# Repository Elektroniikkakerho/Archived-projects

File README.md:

# Elektroniikkakerhon vanhoja projekteja

Tänne on arkistoitu vanhoja projekteja Sähköinsinöörikillan elektroniikkakerhon verkkosivuilta, jotka sijaitsivat vuoteen 2021 asti osoitteessa `http://www.ee.oulu.fi/~elekerho/`. Vaikka tekniikka onkin jo jättänyt osan näistä projekteista jälkeensä, toiset sopivat projekti-ideoiksi vielä tänäkin päivänä. Nämä tomuiset kertomukset voivat myös toimia inspiraationa omille ideoillesi.

### [AVR Speden Spelit](spelit/README.md)

### [Digitaalinen ajastin](ajastin/README.md)

### [Ledinäyttö](ledinaytto/README.md)

### [Ritariässä](ritariassa/README.md)

### [SCART-jäynä](scart/README.md)

### [Selkäsalama](salama/README.md)

### [Taskuradio](taskuradio/README.md)

### [VU-meter](vumeter/README.md)

---

Sähköinsinöörikilta ry 2021

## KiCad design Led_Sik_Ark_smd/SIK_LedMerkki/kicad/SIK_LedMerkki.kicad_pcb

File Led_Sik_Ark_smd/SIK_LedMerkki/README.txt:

Materials required:
L	1	4.7uH
C1-C3	3	100nF
C4	1	4.7u
C5	1	10uF
D1-D49	49	LED
D50	1	D_Schottky
J1	1	Conn_01x06_Female
R1	1	4.7k
R2-R8	7	100
R9	1	976k
R10	1	536k
SW1	1	SW_Push_Dual
U1	1	ATtiny861A-SU
U18	1	MCP1640B

Footprints:
- R & D 0805
- C & L 1206
- MCU SOIC-20W 7.5mm x 12.8mm, pitch 1.27mm
- Pin header pitch 2.54mm
- Regulator SOT-23-6
- CLK TXC_DFN_4SMD

Cover laser cut files:
- Missing, led position file provided. Requires vector conversion + extra space for edge folding

Programming:
- As usual, double check pinout. Programmable through Arduino / other 

Power supply:
- 3V works fine

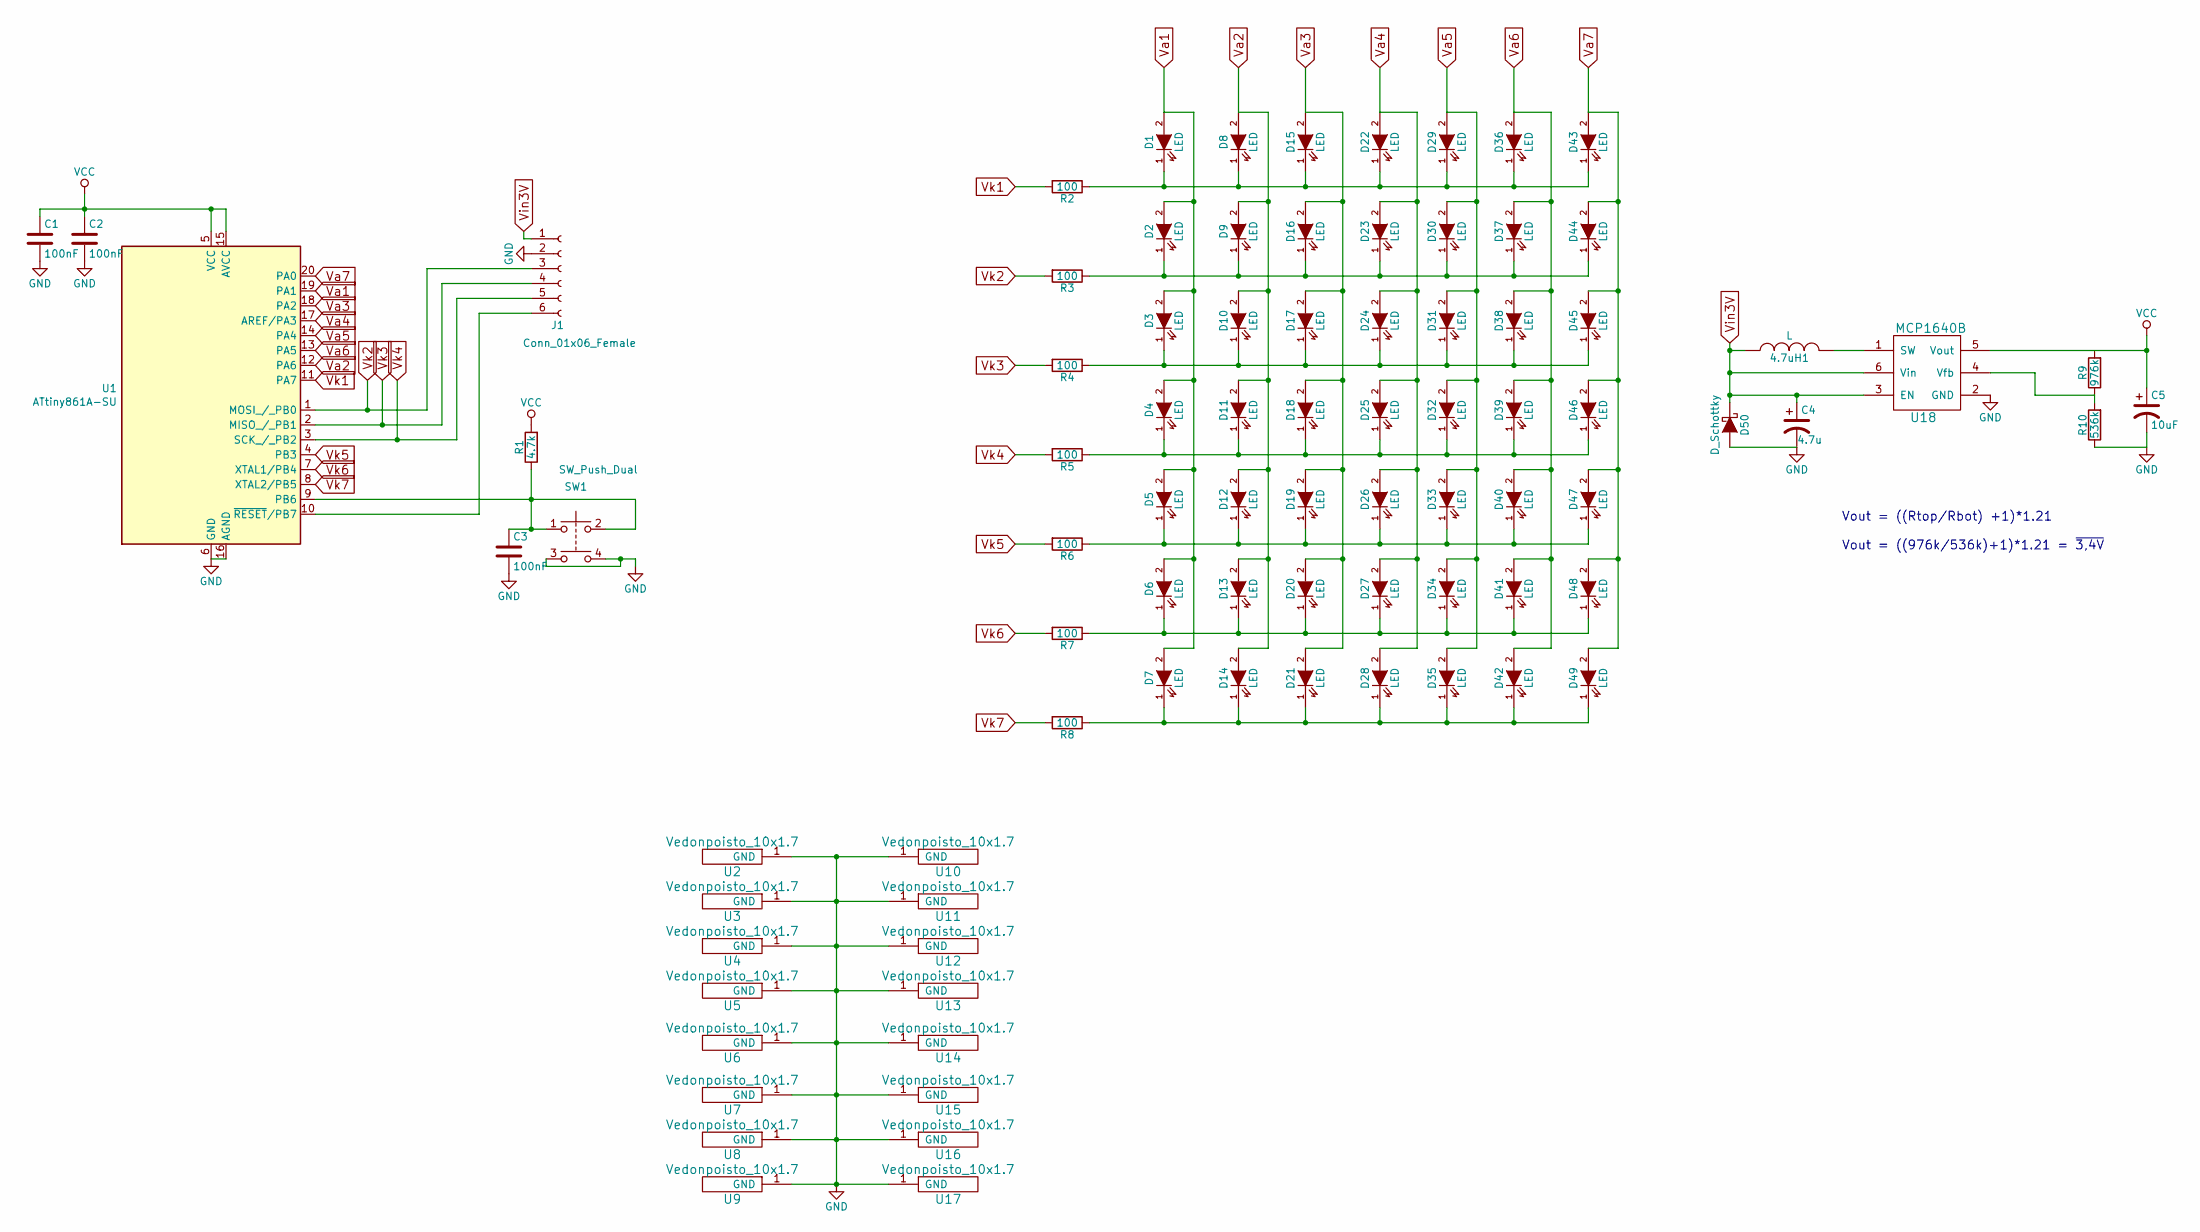
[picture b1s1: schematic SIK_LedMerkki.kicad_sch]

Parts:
4.7uH1: L; L_1210_3225Metric_Pad1.42x2.65mm_HandSolder
C1, C2, C3: 100nF; C_1206_3216Metric_Pad1.42x1.75mm_HandSolder
C4: 4.7u; C_1210_3225Metric_Pad1.42x2.65mm_HandSolder
C5: 10uF; C_1210_3225Metric_Pad1.42x2.65mm_HandSolder
D1, D2, D3, D4, D5, D6, D7, D8, D9, D10, D11, D12, D13, D14, D15, D16, D17, D18, D19, D20, D21, D22, D23, D24, D25, D26, D27, D28, D29, D30, D31, D32, D33, D34, D35, D36, D37, D38, D39, D40, D41, D42, D43, D44, D45, D46, D47, D48, D49: LED; D_0805_2012Metric_Pad1.15x1.40mm_HandSolder
D50: D_Schottky; D_1206_3216Metric_Pad1.42x1.75mm_HandSolder
J1: Conn_01x06_Female; PinHeader_1x06_P2.54mm_Vertical_3mm
R1: 4.7k; R_0805_2012Metric_Pad1.15x1.40mm_HandSolder
R2, R3, R4, R5, R6, R7, R8: 100; R_0805_2012Metric_Pad1.15x1.40mm_HandSolder
R9: 976k; R_0805_2012Metric_Pad1.15x1.40mm_HandSolder
R10: 536k; R_0805_2012Metric_Pad1.15x1.40mm_HandSolder
SW1: SW_Push_Dual; push_switch_SMD
U1: ATtiny861A-SU; SOIC-20W_7.5x12.8mm_P1.27mm_handSolder
U2, U3, U4, U5, U6, U7, U8, U9, U10, U11, U12, U13, U14, U15, U16, U17: Vedonpoisto_10x1.7; vedonpoisto
U18: MCP1640B; SOT-23-6_Handsoldering

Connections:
GND: C1.2, C2.2, C3.2, C4.2, C5.2, D50.2 (A), J1.2, R10.1, SW1.3, SW1.4, U1.6 (GND), U1.16 (AGND), U2.1, U3.1, U4.1, U5.1, U6.1, U7.1, U8.1, U9.1, U10.1, U11.1, U12.1, U13.1, U14.1, U15.1, U16.1, U17.1, U18.2 (GND)
unnamed: 4.7uH1.2, U18.1 (SW)
unnamed: C3.1, R1.1, SW1.1, SW1.2, U1.9 (PB6)
unnamed: D1.1 (K), D8.1 (K), D15.1 (K), D22.1 (K), D29.1 (K), D36.1 (K), D43.1 (K), R2.1
unnamed: D3.1 (K), D10.1 (K), D17.1 (K), D24.1 (K), D31.1 (K), D38.1 (K), D45.1 (K), R4.1
unnamed: D4.1 (K), D11.1 (K), D18.1 (K), D25.1 (K), D32.1 (K), D39.1 (K), D46.1 (K), R5.1
unnamed: D5.1 (K), D12.1 (K), D19.1 (K), D26.1 (K), D33.1 (K), D40.1 (K), D47.1 (K), R6.1
unnamed: D6.1 (K), D13.1 (K), D20.1 (K), D27.1 (K), D34.1 (K), D41.1 (K), D48.1 (K), R7.1
unnamed: D7.1 (K), D14.1 (K), D21.1 (K), D28.1 (K), D35.1 (K), D42.1 (K), D49.1 (K), R8.1
unnamed: D2.1 (K), D9.1 (K), D16.1 (K), D23.1 (K), D30.1 (K), D37.1 (K), D44.1 (K), R3.1
unnamed: J1.6, U1.10 (~RESET/PB7)
unnamed: R9.1, R10.2, U18.4 (Vfb)
VCC: C1.1, C2.1, C5.1, R1.2, R9.2, U1.5 (VCC), U1.15 (AVCC), U18.5 (Vout)
Va1: D1.2 (A), D2.2 (A), D3.2 (A), D4.2 (A), D5.2 (A), D6.2 (A), D7.2 (A), U1.19 (PA1)
Va2: D8.2 (A), D9.2 (A), D10.2 (A), D11.2 (A), D12.2 (A), D13.2 (A), D14.2 (A), U1.12 (PA6)
Va3: D15.2 (A), D16.2 (A), D17.2 (A), D18.2 (A), D19.2 (A), D20.2 (A), D21.2 (A), U1.18 (PA2)
Va4: D22.2 (A), D23.2 (A), D24.2 (A), D25.2 (A), D26.2 (A), D27.2 (A), D28.2 (A), U1.17 (AREF/PA3)
Va5: D29.2 (A), D30.2 (A), D31.2 (A), D32.2 (A), D33.2 (A), D34.2 (A), D35.2 (A), U1.14 (PA4)
Va6: D36.2 (A), D37.2 (A), D38.2 (A), D39.2 (A), D40.2 (A), D41.2 (A), D42.2 (A), U1.13 (PA5)
Va7: D43.2 (A), D44.2 (A), D45.2 (A), D46.2 (A), D47.2 (A), D48.2 (A), D49.2 (A), U1.20 (PA0)
Vin3V: 4.7uH1.1, C4.1, D50.1 (K), J1.1, U18.3 (EN), U18.6 (Vin)
Vk1: R2.2, U1.11 (PA7)
Vk2: J1.3, R3.2, U1.1 (MOSI_/_PB0)
Vk3: J1.4, R4.2, U1.2 (MISO_/_PB1)
Vk4: J1.5, R5.2, U1.3 (SCK_/_PB2)
Vk5: R6.2, U1.4 (PB3)
Vk6: R7.2, U1.7 (XTAL1/PB4)
Vk7: R8.2, U1.8 (XTAL2/PB5)

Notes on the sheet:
Vout = ((Rtop/Rbot) +1)*1.21 Vout = ((976k/536k)+1)*1.21 = ~{3,4V}

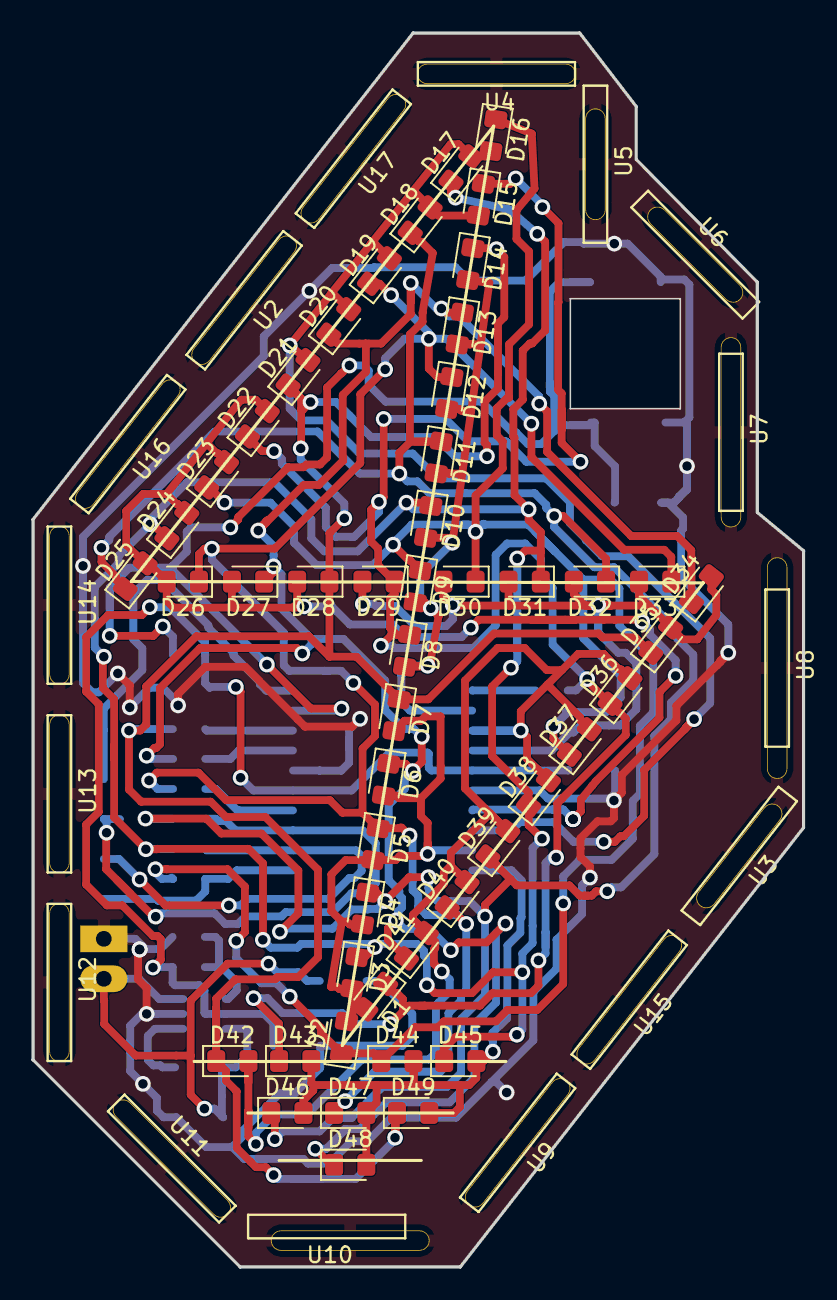
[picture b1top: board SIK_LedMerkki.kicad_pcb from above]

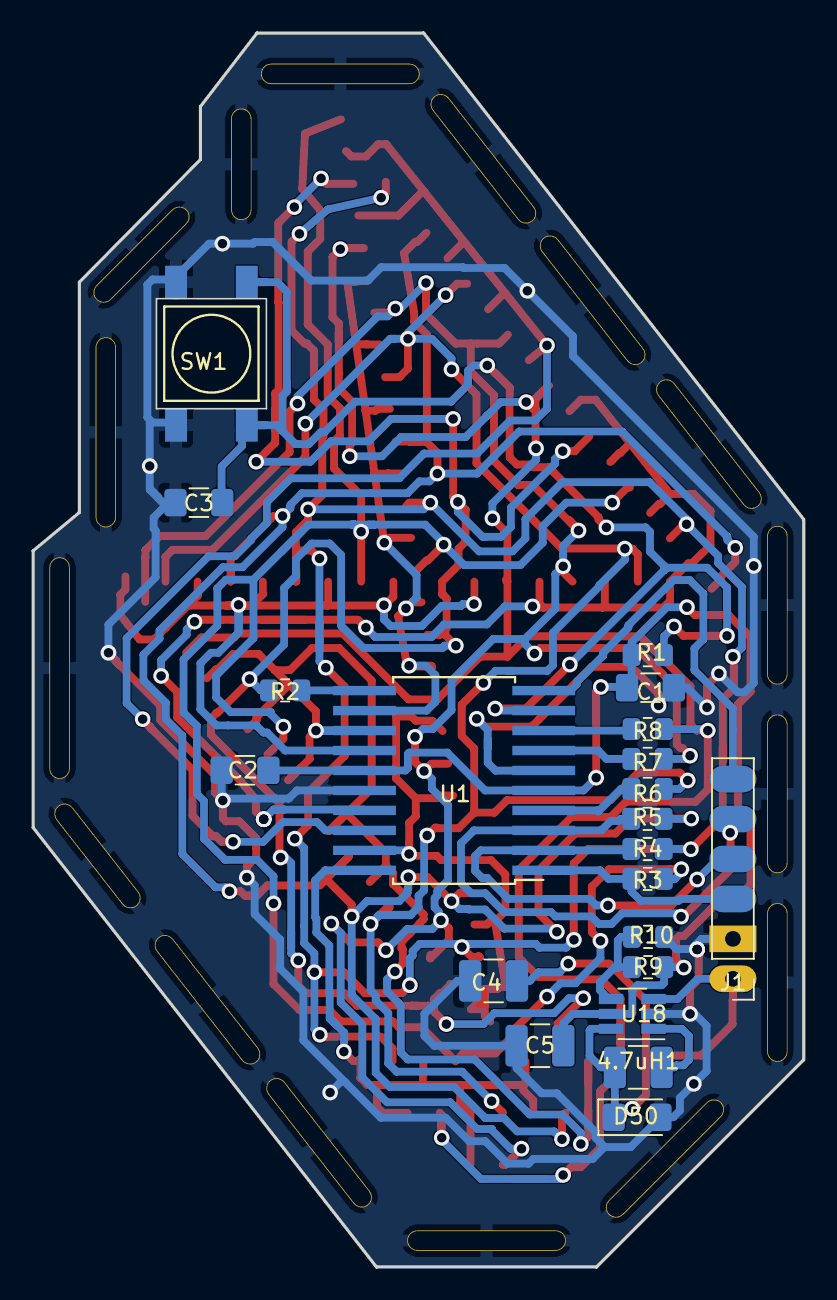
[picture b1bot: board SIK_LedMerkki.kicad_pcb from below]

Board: 2 copper layers, 49.0 x 78.5 mm, 86 parts (21 on the bottom side), 28 nets.

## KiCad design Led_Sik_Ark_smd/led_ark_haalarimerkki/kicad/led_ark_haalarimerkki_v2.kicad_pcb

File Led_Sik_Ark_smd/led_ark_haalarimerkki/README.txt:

Materials required:
C1	1	4.7u
C2, C3	2	22pF
C4	1	10uF
C5-C7	3	100nF
CLK1	1	TXC_7M-50
D1	1	D_Schottky
D2-D91	90	LED
IC1	1	ATMEGA328PB-A
L1	1	4.7uH
P1	1	PWR_1V-5.5V
P2	1	ProgramSPI
R1-R9	9	68
R10	1	820k
R11	1	470k
R12	1	20k
R13	1	4.7k
SW1	1	SW_DPST
U1	1	MCP1640B

Footprints:
- R & D 0805
- C & L 1206
- MCU TQFP-32 7x7mm pitch 0.8mm
- Pin header pitch 2.54mm
- Regulator SOT-23-6
- CLK TXC_DFN_4SMD

Cover laser cut files:
- Available

Programming:
- As usual, double check pinout. Programmable through Arduino / other 

Power supply:
- 3V works fine

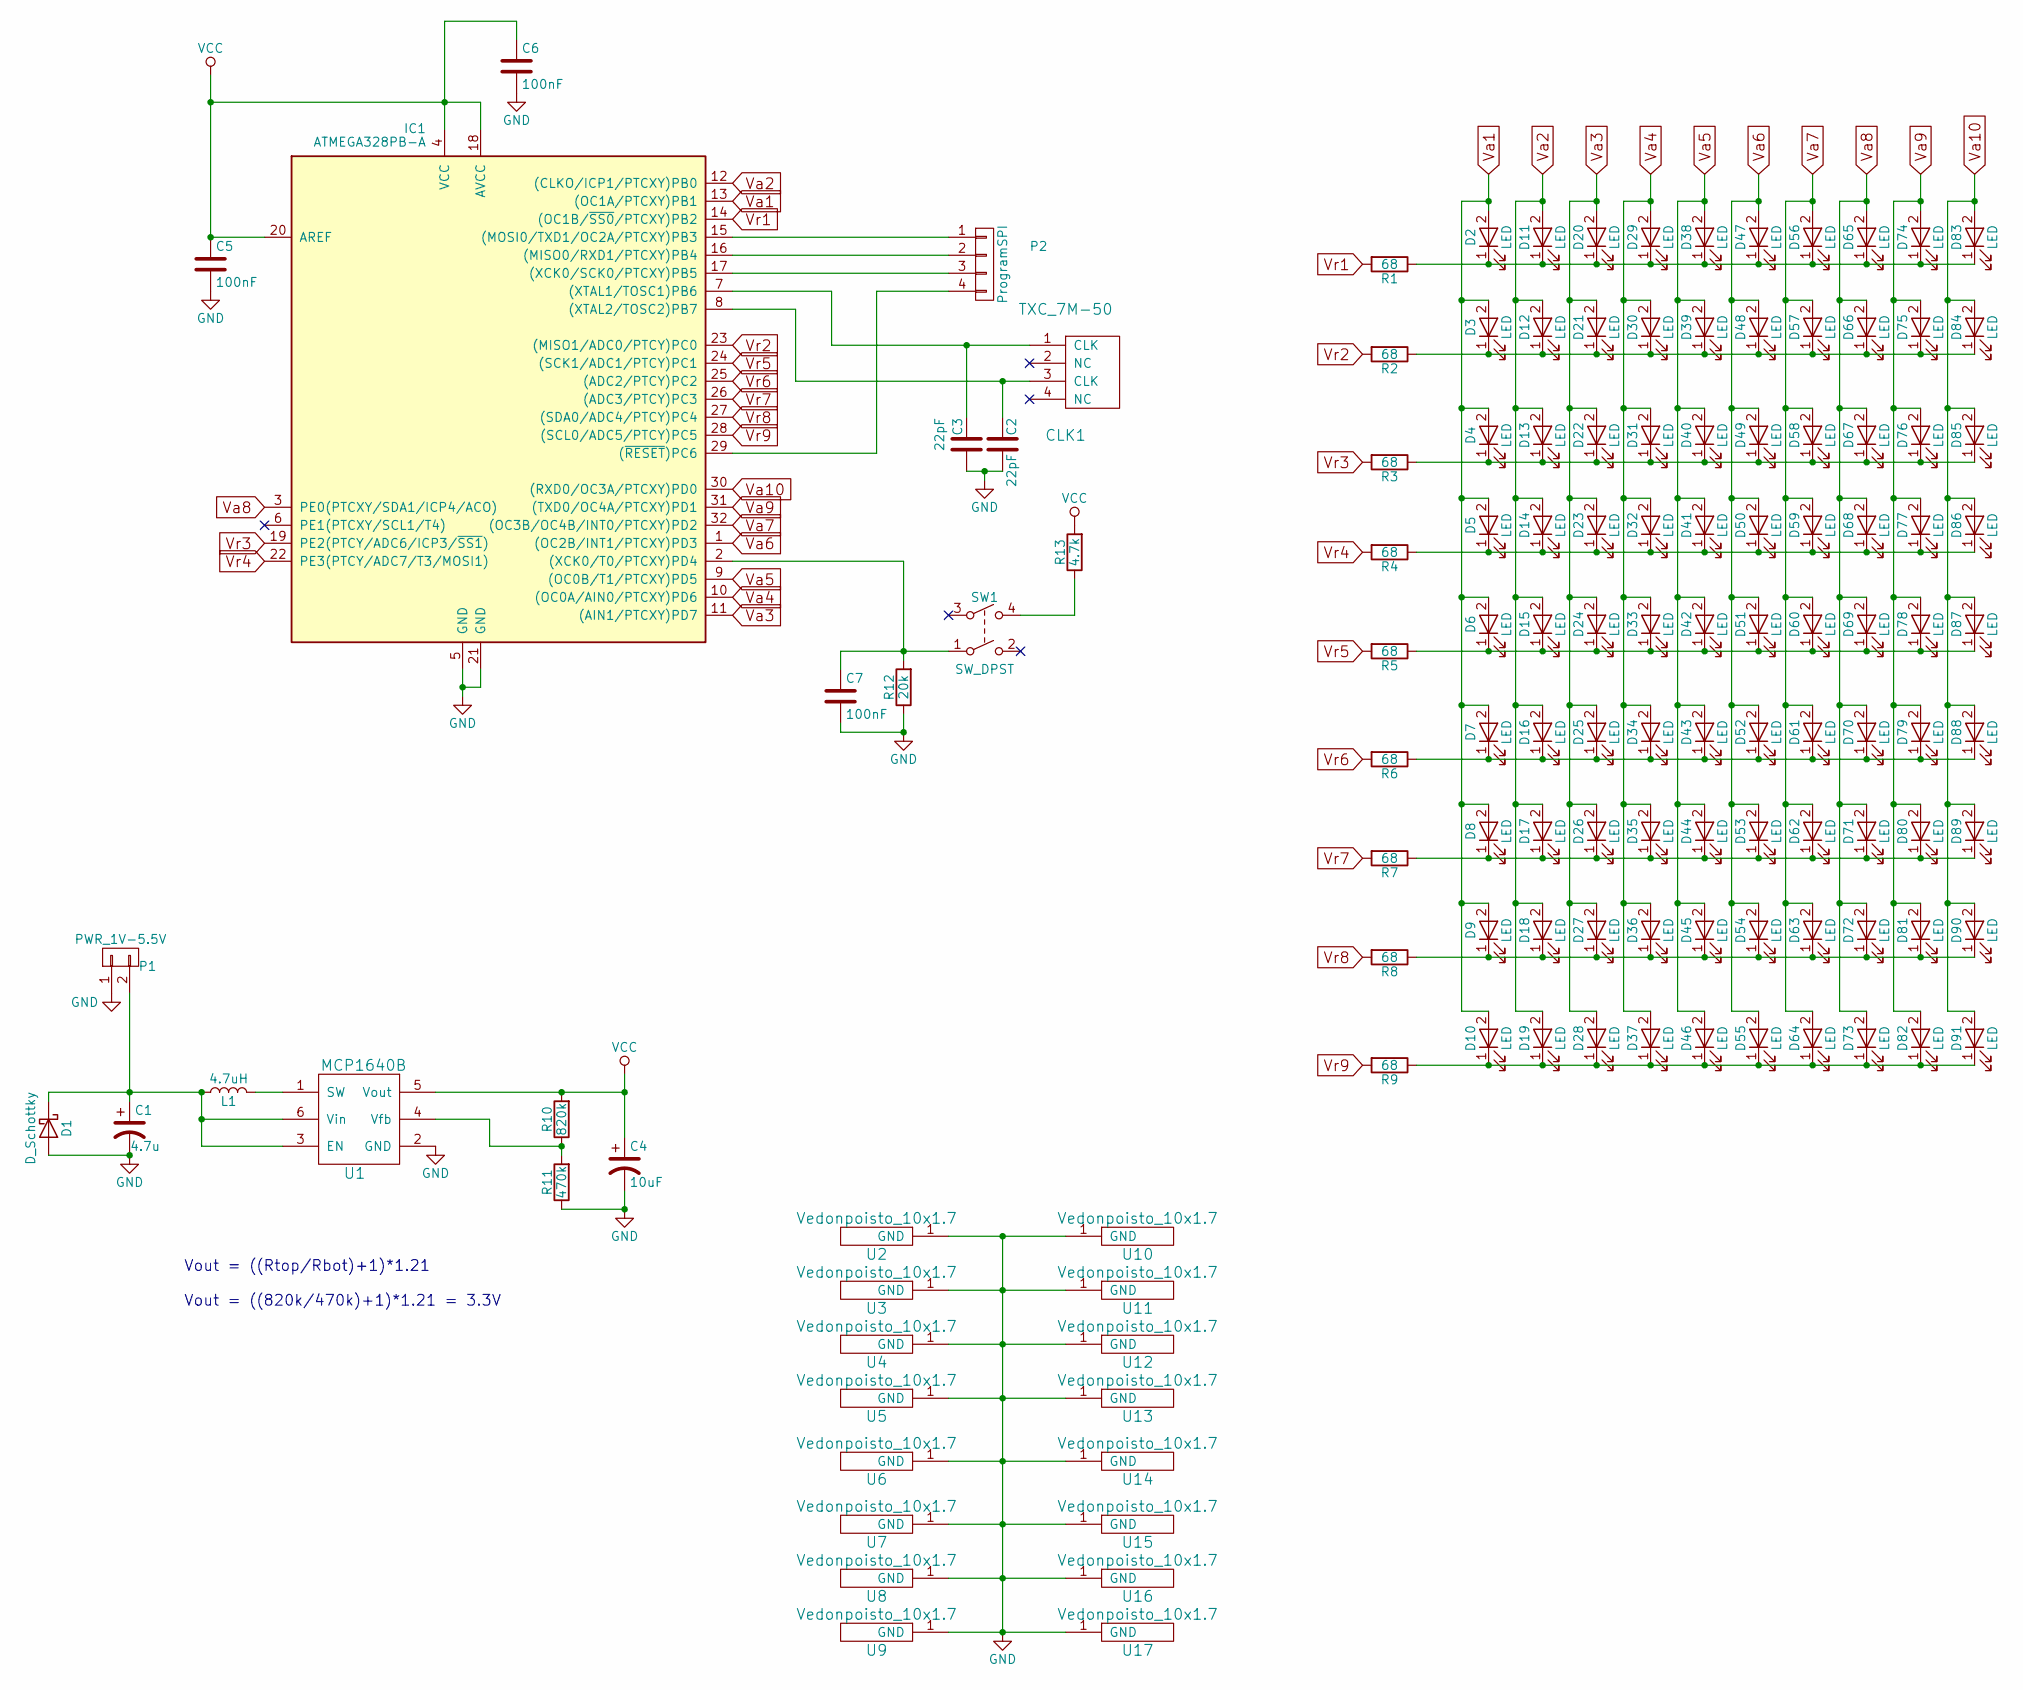
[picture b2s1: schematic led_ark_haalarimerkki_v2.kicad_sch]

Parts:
C1: 4.7u; C_1210_HandSoldering
C2, C3: 22pF; C_1206
C4: 10uF; C_1210_HandSoldering
C5, C6, C7: 100nF; C_1206
CLK1: TXC_7M-50; TXC_DFN_4SMD
D1: D_Schottky; DO-214AC
D2, D3, D4, D5, D6, D7, D8, D9, D10, D11, D12, D13, D14, D15, D16, D17, D18, D19, D20, D21, D22, D23, D24, D25, D26, D27, D28, D29, D30, D31, D32, D33, D34, D35, D36, D37, D38, D39, D40, D41, D42, D43, D44, D45, D46, D47, D48, D49, D50, D51, D52, D53, D54, D55, D56, D57, D58, D59, D60, D61, D62, D63, D64, D65, D66, D67, D68, D69, D70, D71, D72, D73, D74, D75, D76, D77, D78, D79, D80, D81, D82, D83, D84, D85, D86, D87, D88, D89, D90, D91: LED; LED_0805
IC1: ATMEGA328PB-A; TQFP-32_7x7mm_Pitch0.8mm
L1: 4.7uH; R_1210_HandSoldering
P1: PWR_1V-5.5V; Pin_Header_Straight_1x02_Pitch2.54mm
P2: ProgramSPI; Pin_Header_Straight_1x04_Pitch2.54mm
R1, R2, R3, R4, R5, R6, R7, R8, R9: 68; R_0805_HandSoldering
R10: 820k; R_0805_HandSoldering
R11: 470k; R_0805_HandSoldering
R12: 20k; R_0805_HandSoldering
R13: 4.7k; R_0805_HandSoldering
SW1: SW_DPST; push_switch_SMD
U1: MCP1640B; SOT-23-6
U2, U3, U4, U5, U6, U7, U8, U9, U10, U11, U12, U13, U14, U15, U16, U17: Vedonpoisto_10x1.7; vedonpoisto

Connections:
GND: C1.2, C2.1, C3.1, C4.2, C5.2, C6.2, C7.2, D1.2 (A), IC1.5 (GND), IC1.21 (GND), P1.1, R11.1, R12.1, U1.2 (GND), U2.1, U3.1, U4.1, U5.1, U6.1, U7.1, U8.1, U9.1, U10.1, U11.1, U12.1, U13.1, U14.1, U15.1, U16.1, U17.1
unnamed: C1.1, D1.1 (K), L1.1, P1.2, U1.3 (EN), U1.6 (Vin)
unnamed: C2.2, CLK1.3 (CLK), IC1.8 ((XTAL2/TOSC2)PB7)
unnamed: C3.2, CLK1.1 (CLK), IC1.7 ((XTAL1/TOSC1)PB6)
unnamed: C7.1, IC1.2 ((XCK0/T0/PTCXY)PD4), R12.2, SW1.1
unnamed: D10.1 (K), D19.1 (K), D28.1 (K), D37.1 (K), D46.1 (K), D55.1 (K), D64.1 (K), D73.1 (K), D82.1 (K), D91.1 (K), R9.1
unnamed: D2.1 (K), D11.1 (K), D20.1 (K), D29.1 (K), D38.1 (K), D47.1 (K), D56.1 (K), D65.1 (K), D74.1 (K), D83.1 (K), R1.1
unnamed: D3.1 (K), D12.1 (K), D21.1 (K), D30.1 (K), D39.1 (K), D48.1 (K), D57.1 (K), D66.1 (K), D75.1 (K), D84.1 (K), R2.1
unnamed: D4.1 (K), D13.1 (K), D22.1 (K), D31.1 (K), D40.1 (K), D49.1 (K), D58.1 (K), D67.1 (K), D76.1 (K), D85.1 (K), R3.1
unnamed: D5.1 (K), D14.1 (K), D23.1 (K), D32.1 (K), D41.1 (K), D50.1 (K), D59.1 (K), D68.1 (K), D77.1 (K), D86.1 (K), R4.1
unnamed: D6.1 (K), D15.1 (K), D24.1 (K), D33.1 (K), D42.1 (K), D51.1 (K), D60.1 (K), D69.1 (K), D78.1 (K), D87.1 (K), R5.1
unnamed: D7.1 (K), D16.1 (K), D25.1 (K), D34.1 (K), D43.1 (K), D52.1 (K), D61.1 (K), D70.1 (K), D79.1 (K), D88.1 (K), R6.1
unnamed: D8.1 (K), D17.1 (K), D26.1 (K), D35.1 (K), D44.1 (K), D53.1 (K), D62.1 (K), D71.1 (K), D80.1 (K), D89.1 (K), R7.1
unnamed: D9.1 (K), D18.1 (K), D27.1 (K), D36.1 (K), D45.1 (K), D54.1 (K), D63.1 (K), D72.1 (K), D81.1 (K), D90.1 (K), R8.1
unnamed: IC1.15 ((MOSI0/TXD1/OC2A/PTCXY)PB3), P2.1
unnamed: IC1.16 ((MISO0/RXD1/PTCXY)PB4), P2.2
unnamed: IC1.17 ((XCK0/SCK0/PTCXY)PB5), P2.3
unnamed: IC1.29 ((~RESET)PC6), P2.4
unnamed: L1.2, U1.1 (SW)
unnamed: R10.1, R11.2, U1.4 (Vfb)
unnamed: R13.1, SW1.4
VCC: C4.1, C5.1, C6.1, IC1.4 (VCC), IC1.18 (AVCC), IC1.20 (AREF), R10.2, R13.2, U1.5 (Vout)
Va1: D2.2 (A), D3.2 (A), D4.2 (A), D5.2 (A), D6.2 (A), D7.2 (A), D8.2 (A), D9.2 (A), D10.2 (A), IC1.13 ((OC1A/PTCXY)PB1)
Va2: D11.2 (A), D12.2 (A), D13.2 (A), D14.2 (A), D15.2 (A), D16.2 (A), D17.2 (A), D18.2 (A), D19.2 (A), IC1.12 ((CLKO/ICP1/PTCXY)PB0)
Va3: D20.2 (A), D21.2 (A), D22.2 (A), D23.2 (A), D24.2 (A), D25.2 (A), D26.2 (A), D27.2 (A), D28.2 (A), IC1.11 ((AIN1/PTCXY)PD7)
Va4: D29.2 (A), D30.2 (A), D31.2 (A), D32.2 (A), D33.2 (A), D34.2 (A), D35.2 (A), D36.2 (A), D37.2 (A), IC1.10 ((OC0A/AIN0/PTCXY)PD6)
Va5: D38.2 (A), D39.2 (A), D40.2 (A), D41.2 (A), D42.2 (A), D43.2 (A), D44.2 (A), D45.2 (A), D46.2 (A), IC1.9 ((OC0B/T1/PTCXY)PD5)
Va6: D47.2 (A), D48.2 (A), D49.2 (A), D50.2 (A), D51.2 (A), D52.2 (A), D53.2 (A), D54.2 (A), D55.2 (A), IC1.1 ((OC2B/INT1/PTCXY)PD3)
Va7: D56.2 (A), D57.2 (A), D58.2 (A), D59.2 (A), D60.2 (A), D61.2 (A), D62.2 (A), D63.2 (A), D64.2 (A), IC1.32 ((OC3B/OC4B/INT0/PTCXY)PD2)
Va8: D65.2 (A), D66.2 (A), D67.2 (A), D68.2 (A), D69.2 (A), D70.2 (A), D71.2 (A), D72.2 (A), D73.2 (A), IC1.3 (PE0(PTCXY/SDA1/ICP4/ACO))
Va9: D74.2 (A), D75.2 (A), D76.2 (A), D77.2 (A), D78.2 (A), D79.2 (A), D80.2 (A), D81.2 (A), D82.2 (A), IC1.31 ((TXD0/OC4A/PTCXY)PD1)
Va10: D83.2 (A), D84.2 (A), D85.2 (A), D86.2 (A), D87.2 (A), D88.2 (A), D89.2 (A), D90.2 (A), D91.2 (A), IC1.30 ((RXD0/OC3A/PTCXY)PD0)
Vr1: IC1.14 ((OC1B/~SS0/PTCXY)PB2), R1.2
Vr2: IC1.23 ((MISO1/ADC0/PTCY)PC0), R2.2
Vr3: IC1.19 (PE2(PTCY/ADC6/ICP3/~SS1)), R3.2
Vr4: IC1.22 (PE3(PTCY/ADC7/T3/MOSI1)), R4.2
Vr5: IC1.24 ((SCK1/ADC1/PTCY)PC1), R5.2
Vr6: IC1.25 ((ADC2/PTCY)PC2), R6.2
Vr7: IC1.26 ((ADC3/PTCY)PC3), R7.2
Vr8: IC1.27 ((SDA0/ADC4/PTCY)PC4), R8.2
Vr9: IC1.28 ((SCL0/ADC5/PTCY)PC5), R9.2

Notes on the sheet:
Vout = ((Rtop/Rbot)+1)*1.21 Vout = ((820k/470k)+1)*1.21 = 3.3V

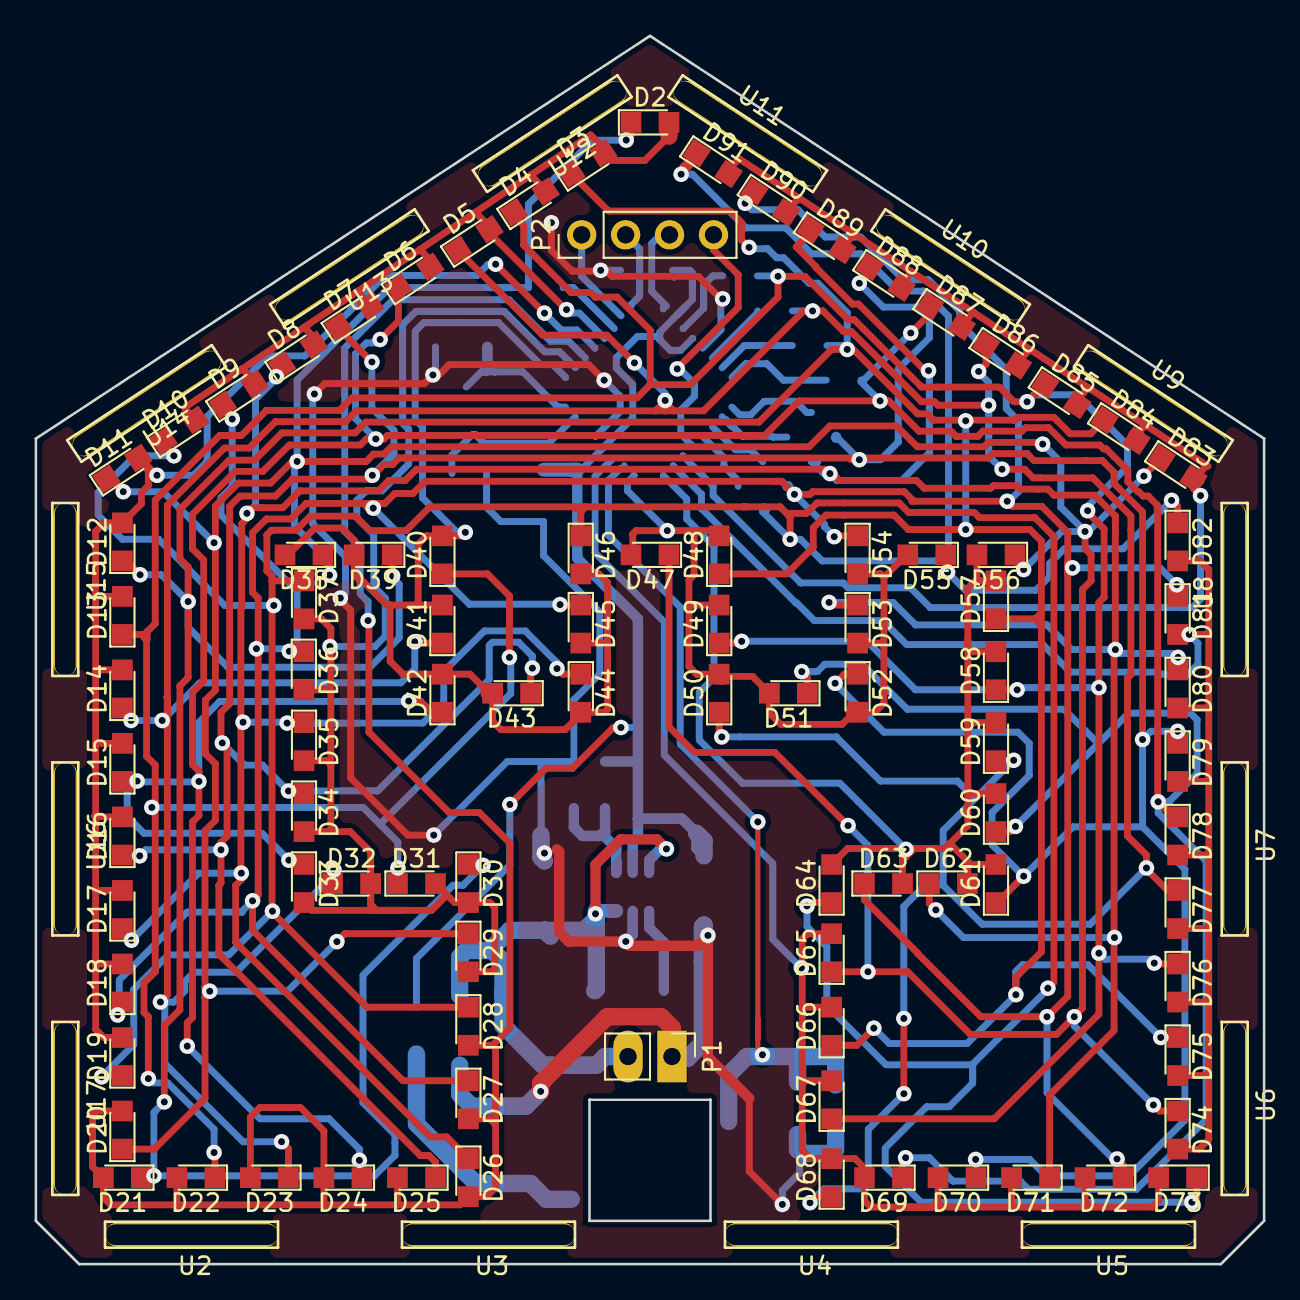
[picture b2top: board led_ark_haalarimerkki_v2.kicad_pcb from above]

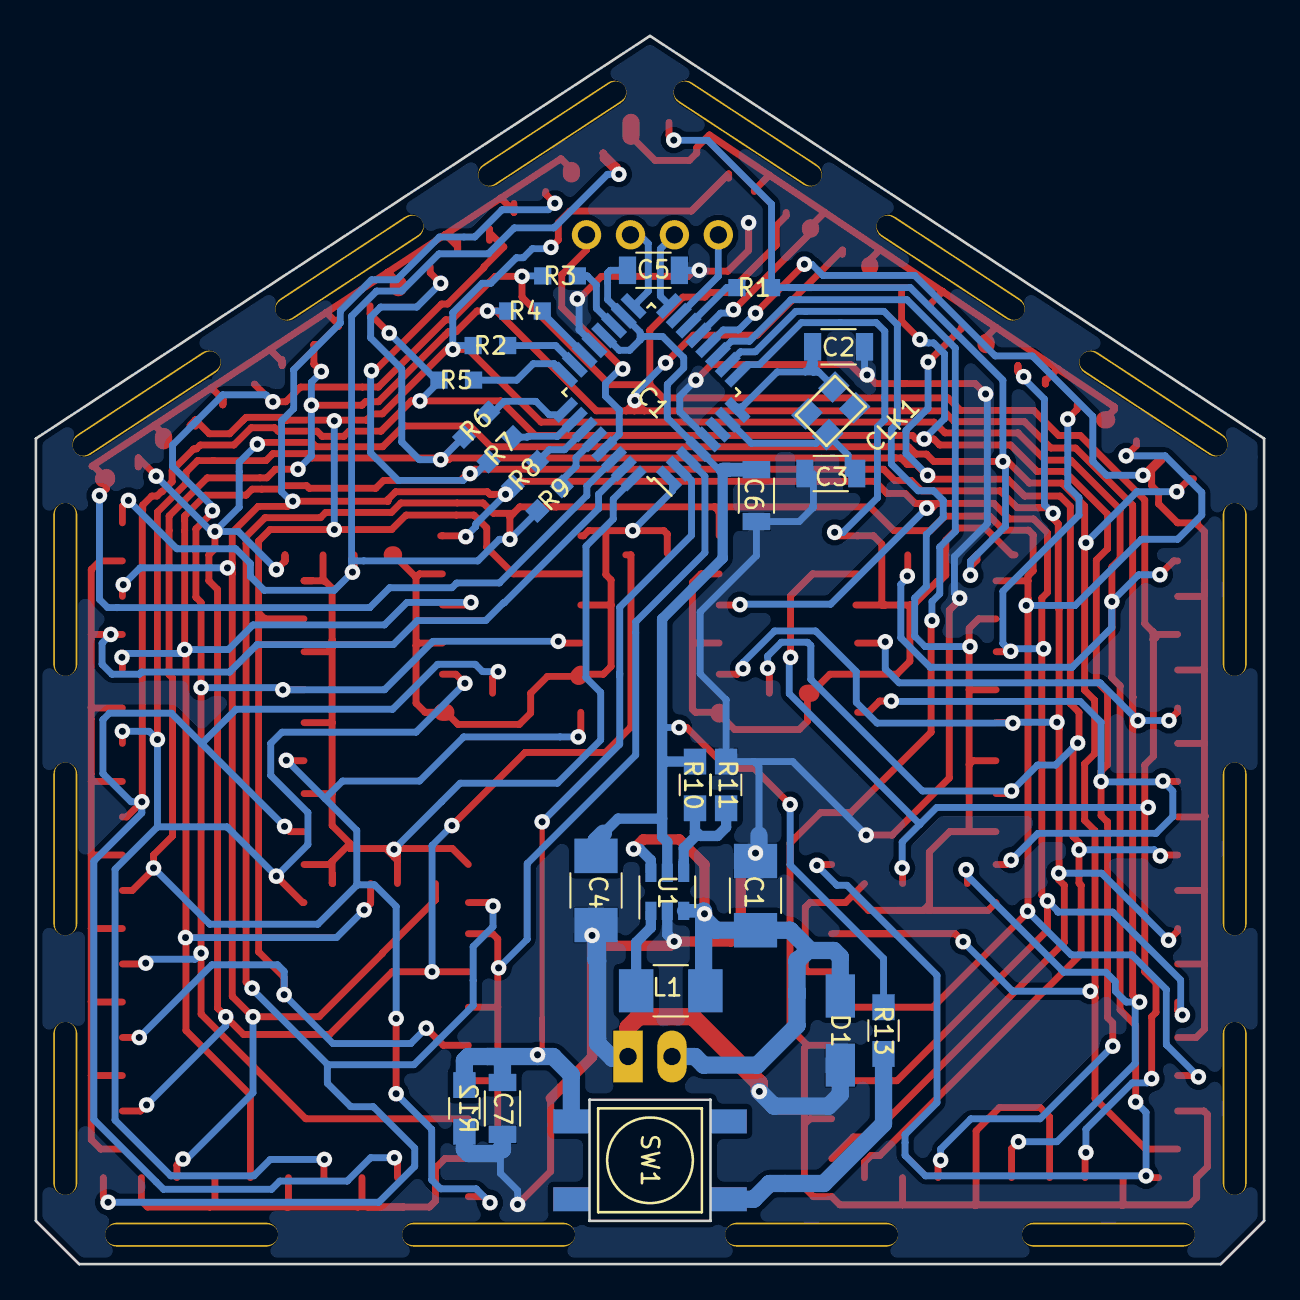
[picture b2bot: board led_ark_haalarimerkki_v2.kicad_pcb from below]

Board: 2 copper layers, 71.0 x 71.0 mm, 134 parts (26 on the bottom side), 41 nets.

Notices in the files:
Led_Sik_Ark_smd/SIK_LedMerkki/kicad/SIK_LedMerkki.kicad_sch:
© Niko Huttula
